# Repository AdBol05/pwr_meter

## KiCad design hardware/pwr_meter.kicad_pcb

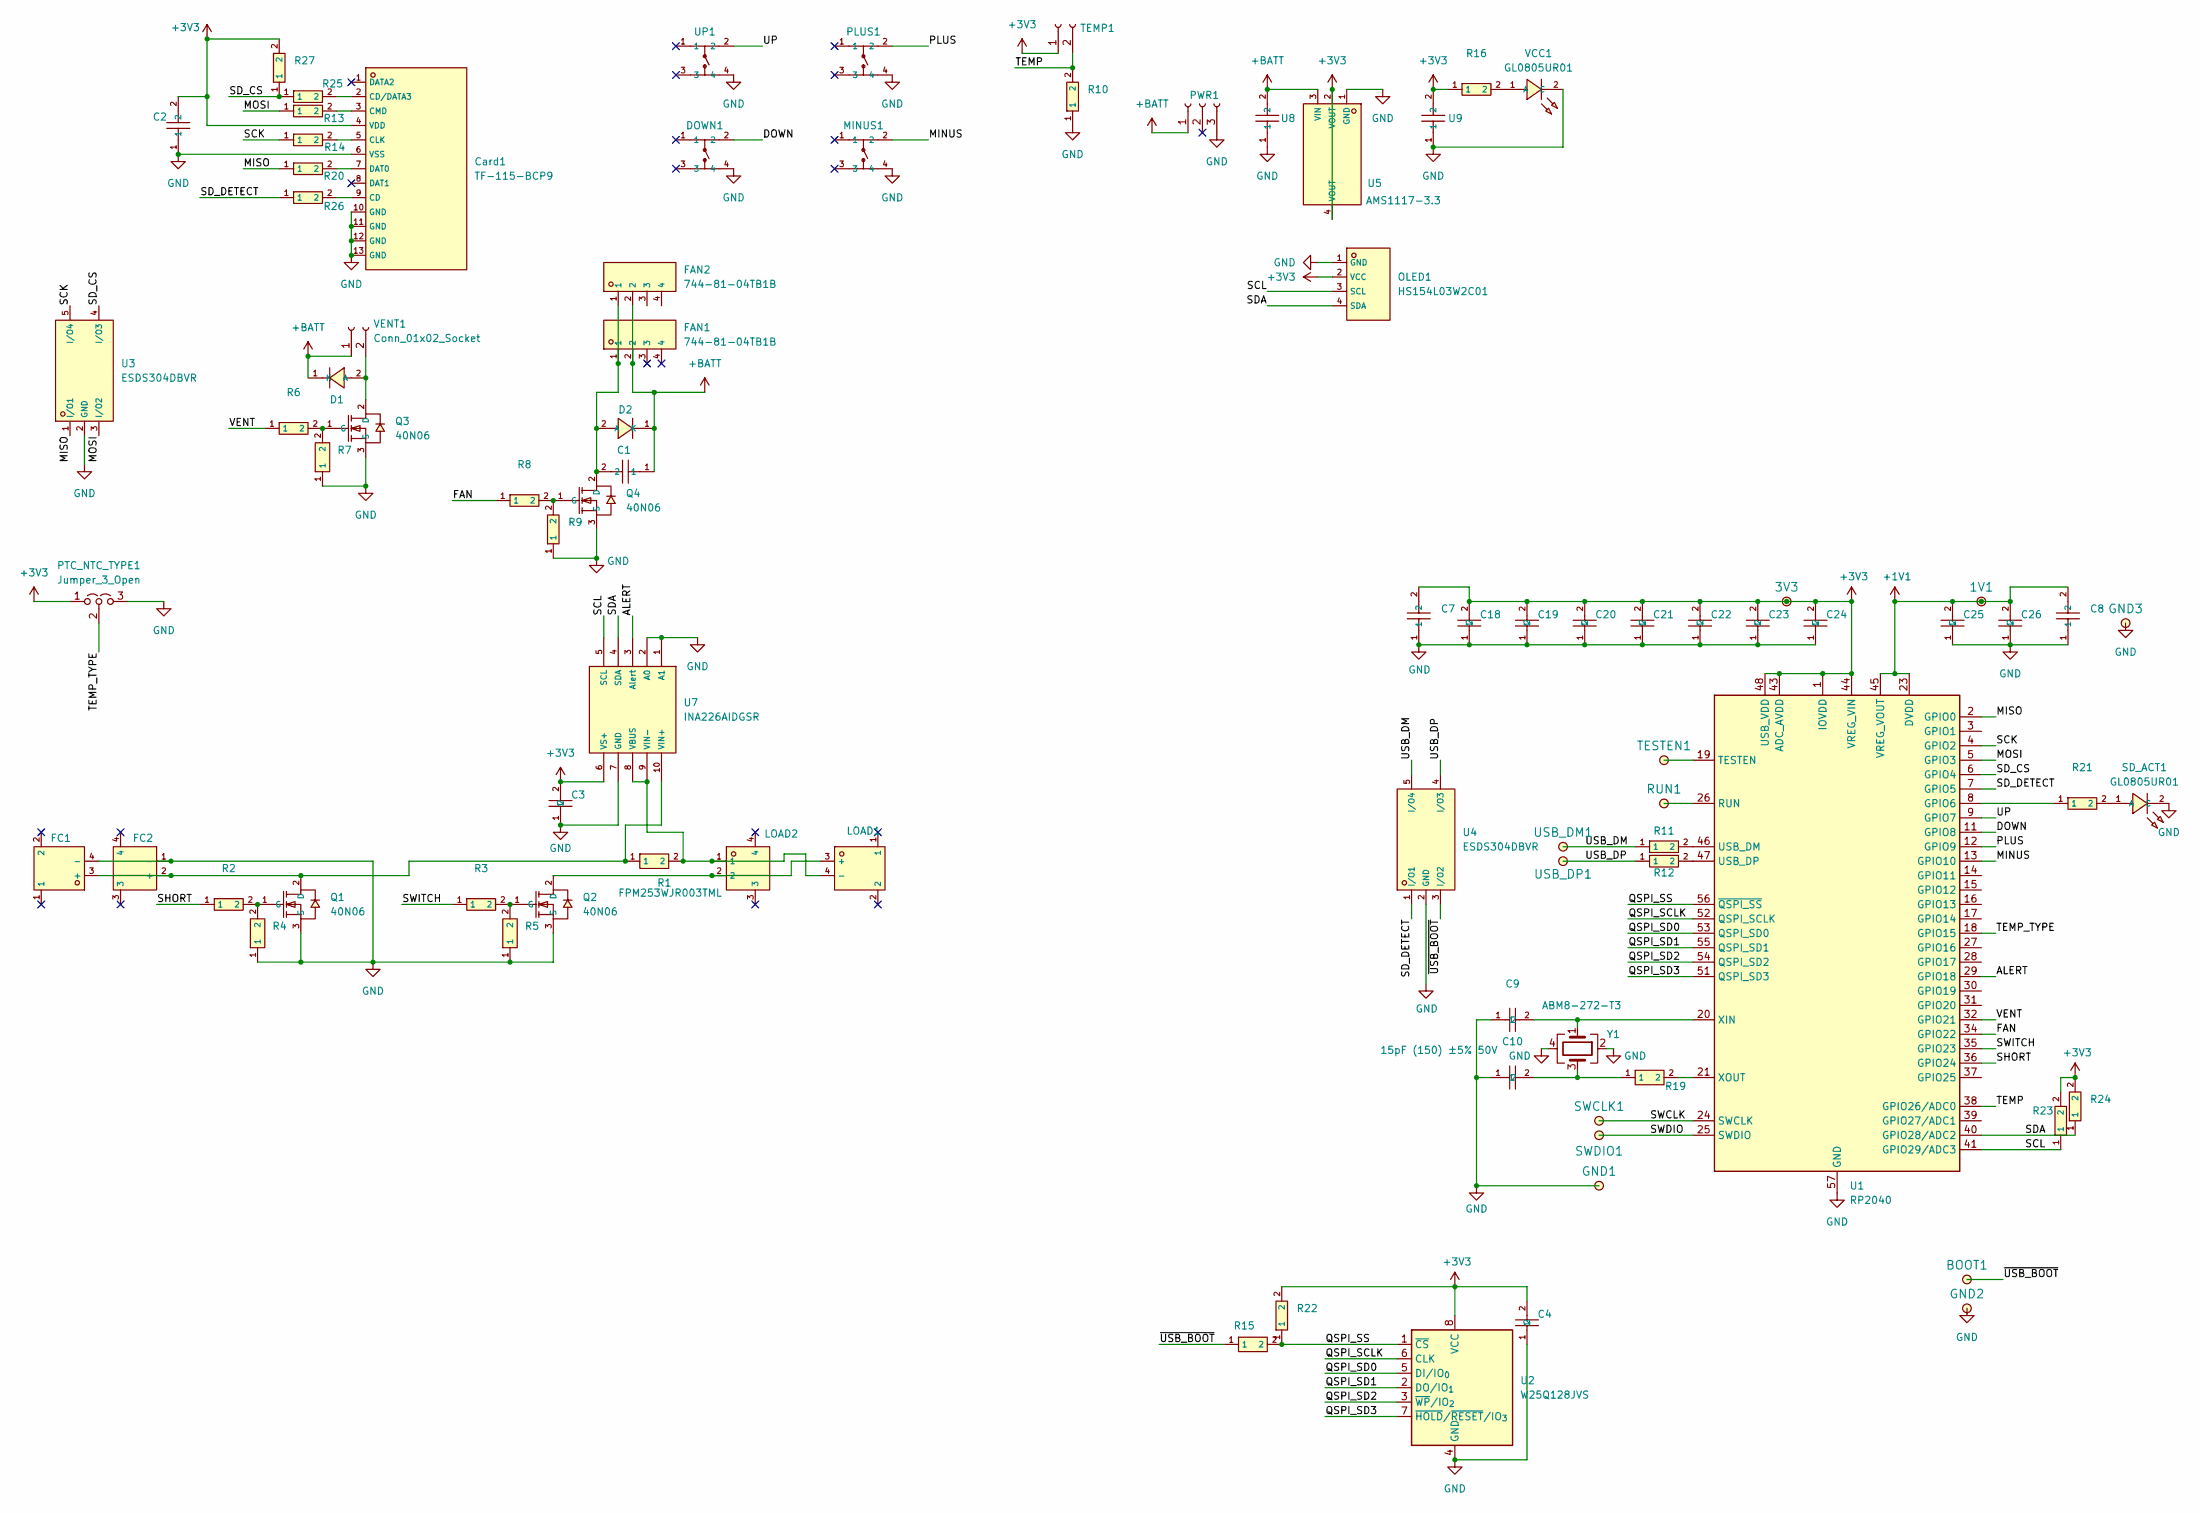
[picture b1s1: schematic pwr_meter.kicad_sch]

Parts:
1V1, 3V3: ${FAMILY}; TestPoint_Pad_1.0x1.0mm
BOOT1: ${FAMILY}; TestPoint_Pad_1.0x1.0mm
C1, C2: LMK107BBJ106MALT; C195004_C0603; LCSC C195004
C3, C4, C18, C19, C20, C21, C22, C23, C24, C25, C26: CC0603JRX7R9BB104; C91183_C0603; LCSC C91183
C7, C8: 2F01MC105B3K7D0; C54824954_C0603; LCSC C54824954
C9, C10: 15pF (150) ±5% 50V; C1644_C0603; LCSC C1644
Card1: TF-115-BCP9; C720505_TF-SMD_TF-115-BCP9; LCSC C720505
D1, D2: 1N4007_C2892681; C2892681_SOD-123FL_L2_8-W1_8-LS3_7-RD; LCSC C2892681
DOWN1: TS1103S-12X12X7.5DIP; C48677982_SW-TH_4P-L12_0-W12_0-P5_00-LS12_5; LCSC C48677982
FAN1, FAN2: 744-81-04TB1B; C402774_CONN-TH_4P-P2_54-V-M_744-81-04TXXX; LCSC C402774
FC1: FC1; C428722_TH_2P-XT60PW-F; LCSC C428722
FC2: XT30PW-M; C431092_CONN-TH_XT30PW-M; LCSC C431092
GND1, GND2, GND3: ${FAMILY}; TestPoint_Pad_1.0x1.0mm
LOAD1: XT60PW-F_C428722; C428722_TH_2P-XT60PW-F; LCSC C428722
LOAD2: XT30PW-F; C2913282_CONN-TH_XT30PW-F-1; LCSC C2913282
MINUS1: TS1103S-12X12X7.5DIP; C48677982_SW-TH_4P-L12_0-W12_0-P5_00-LS12_5; LCSC C48677982
OLED1: HS154L03W2C01; C7465999_OLED-TH_-4P-L42_4-W38_0-P2_54; LCSC C7465999
PLUS1: TS1103S-12X12X7.5DIP; C48677982_SW-TH_4P-L12_0-W12_0-P5_00-LS12_5; LCSC C48677982
PTC_NTC_TYPE1: Jumper_3_Open; SolderJumper-3_P1.3mm_Open_RoundedPad1.0x1.5mm
PWR1: Conn_01x03_Socket; PinSocket_1x03_P2.54mm_Vertical
Q1, Q2, Q3, Q4: 40N06; C668202_TO-252-2_L6_6-W6_1-P4_57-LS9_9-BR-CW; LCSC C668202
R1: FPM253WJR003TML; C7420043_RES-SMD_L6_3-W3_2_R2512; LCSC C7420043
R2, R3, R6, R8, R13, R14, R16, R20, R21, R25, R26: CR0603FA1000G; C100700_R0603; LCSC C100700
R4, R5, R7: FRC0603F1004TS; C2907003_R0603; LCSC C2907003
R9, R10, R22, R23, R24, R27: RTT03103JTP; C103210_R0603; LCSC C103210
R11, R12: MCR03ERTJ270; C308128_R0603; LCSC C308128
R15, R19: HRC0603J102 ENTN; C54920984_R0603; LCSC C54920984
RUN1: ${FAMILY}; TestPoint_Pad_1.0x1.0mm
SD_ACT1: GL0805UR01; C51933307_LED0805-R-RD_RED; LCSC C51933307
SWCLK1: ${FAMILY}; TestPoint_Pad_1.0x1.0mm
SWDIO1: ${FAMILY}; TestPoint_Pad_1.0x1.0mm
TEMP1: Conn_01x02_Socket; PinSocket_1x02_P2.54mm_Vertical
TESTEN1: ${FAMILY}; TestPoint_Pad_1.0x1.0mm
U1: RP2040; QFN-56-1EP_7x7mm_P0.4mm_EP3.2x3.2mm
U2: W25Q128JVS; SOIC-8_5.3x5.3mm_P1.27mm
U3, U4: ESDS304DBVR; C1847869_SOT-23-5_L2_9-W1_6-P0_95-LS2_8-BR; LCSC C1847869
U5: AMS1117-3.3; C6186_SOT-223-3_L6_5-W3_4-P2_30-LS7_0-BR; LCSC C6186
U7: INA226AIDGSR; C49851_MSOP-10_L3_0-W3_0-P0_50-LS5_0-BL; LCSC C49851
U8, U9: HGC1210R5107M160NSVK; C7432790_C1210; LCSC C7432790
UP1: TS1103S-12X12X7.5DIP; C48677982_SW-TH_4P-L12_0-W12_0-P5_00-LS12_5; LCSC C48677982
USB_DM1: ${FAMILY}; TestPoint_Pad_1.0x1.0mm
USB_DP1: ${FAMILY}; TestPoint_Pad_1.0x1.0mm
VCC1: GL0805UR01; C51933307_LED0805-R-RD_RED; LCSC C51933307
VENT1: Conn_01x02_Socket; PinSocket_1x02_P2.54mm_Vertical
Y1: ABM8-272-T3; Crystal_SMD_3225-4Pin_3.2x2.5mm

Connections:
+1V1: 1V1.1 (1_1), C8.2, C25.2, C26.2, U1.23 (DVDD), U1.45 (VREG_VOUT), U1.50 (DVDD)
+3V3: 3V3.1 (1_1), C2.2, C3.2, C4.2, C7.2, C18.2, C19.2, C20.2, C21.2, C22.2, C23.2, C24.2, Card1.4 (VDD), OLED1.2 (VCC), PTC_NTC_TYPE1.1 (A), R16.1, R22.2, R23.2, R24.2, R27.2, TEMP1.1, U1.1 (IOVDD), U1.10 (IOVDD), U1.22 (IOVDD), U1.33 (IOVDD), U1.42 (IOVDD), U1.43 (ADC_AVDD), U1.44 (VREG_VIN), U1.48 (USB_VDD), U1.49 (IOVDD), U2.8 (VCC), U5.2 (VOUT), U5.4 (VOUT), U7.6 (VS+), U9.2
+BATT: C1.1, D1.1 (K), D2.1 (K), FAN1.2, FAN2.2, PWR1.1, U5.3 (VIN), U8.2, VENT1.1
/ALERT: U1.29 (GPIO18), U7.3 (Alert)
/DOWN: DOWN1.2, U1.11 (GPIO8)
/FAN: R8.1, U1.34 (GPIO22)
/MINUS: MINUS1.2, U1.13 (GPIO10)
/MISO: R20.1, U1.2 (GPIO0), U3.1 (I/O1)
/MOSI: R13.1, U1.5 (GPIO3), U3.3 (I/O2)
/PLUS: PLUS1.2, U1.12 (GPIO9)
/QSPI_SCLK: U1.52 (QSPI_SCLK), U2.6 (CLK)
/QSPI_SD0: U1.53 (QSPI_SD0), U2.5 (DI/IO_{0})
/QSPI_SD1: U1.55 (QSPI_SD1), U2.2 (DO/IO_{1})
/QSPI_SD2: U1.54 (QSPI_SD2), U2.3 (~WP/IO_{2})
/QSPI_SD3: U1.51 (QSPI_SD3), U2.7 (~HOLD/~RESET/IO_{3})
/QSPI_SS: R15.2, R22.1, U1.56 (~QSPI_SS), U2.1 (~CS)
/SCK: R14.1, U1.4 (GPIO2), U3.5 (I/O4)
/SCL: OLED1.3 (SCL), R23.1, U1.41 (GPIO29/ADC3), U7.5 (SCL)
/SDA: OLED1.4 (SDA), R24.1, U1.40 (GPIO28/ADC2), U7.4 (SDA)
/SD_CS: R25.1, R27.1, U1.6 (GPIO4), U3.4 (I/O3)
/SD_DETECT: R26.1, U1.7 (GPIO5), U4.1 (I/O1)
/SHORT: R2.1, U1.36 (GPIO24)
/SWCLK: SWCLK1.1 (1_1), U1.24 (SWCLK)
/SWDIO: SWDIO1.1 (1_1), U1.25 (SWDIO)
/SWITCH: R3.1, U1.35 (GPIO23)
/TEMP: R10.2, TEMP1.2, U1.38 (GPIO26/ADC0)
/TEMP_TYPE: PTC_NTC_TYPE1.2 (C), U1.18 (GPIO15)
/UP: U1.9 (GPIO7), UP1.2
/USB_DM: R11.1, U4.5 (I/O4), USB_DM1.1 (1_1)
/USB_DP: R12.1, U4.4 (I/O3), USB_DP1.1 (1_1)
/VENT: R6.1, U1.32 (GPIO21)
/~USB_BOOT: BOOT1.1 (1_1), R15.1, U4.3 (I/O2)
GND: C2.1, C3.1, C4.1, C7.1, C8.1, C9.1, C10.1, C18.1, C19.1, C20.1, C21.1, C22.1, C23.1, C24.1, C25.1, C26.1, Card1.6 (VSS), Card1.10 (GND), Card1.11 (GND), Card1.12 (GND), Card1.13 (GND), DOWN1.4, FC1.4 (-), FC2.1 (-), GND1.1 (1_1), GND2.1 (1_1), GND3.1 (1_1), MINUS1.4, OLED1.1 (GND), PLUS1.4, PTC_NTC_TYPE1.3 (B), PWR1.3, Q1.3 (S), Q2.3 (S), Q3.3 (S), Q4.3 (S), R4.1, R5.1, R7.1, R9.1, R10.1, SD_ACT1.2 (C), U1.57 (GND), U2.4 (GND), U3.2 (GND), U4.2 (GND), U5.1 (GND), U7.1 (A1), U7.2 (A0), U7.7 (GND), U8.1, U9.1, UP1.4, VCC1.2 (C), Y1.2, Y1.4
unnamed: C10.2, R19.1, Y1.3
unnamed: Card1.9 (CD), R26.2
unnamed: Card1.2 (CD/DATA3), R25.2
unnamed: Card1.5 (CLK), R14.2
unnamed: Card1.3 (CMD), R13.2
unnamed: Card1.7 (DAT0), R20.2
unnamed: D1.2 (A), Q3.2 (D), VENT1.2
unnamed: C1.2, D2.2 (A), FAN1.1, FAN2.1, Q4.2 (D)
unnamed: FC1.3 (+), FC2.2 (+), Q1.2 (D), R1.1, U7.10 (VIN+)
unnamed: LOAD1.3 (+), LOAD2.2, Q2.2 (D)
unnamed: LOAD1.4 (-), LOAD2.1, R1.2, U7.8 (VBUS), U7.9 (VIN-)
unnamed: Q1.1 (G), R2.2, R4.2
unnamed: Q2.1 (G), R3.2, R5.2
unnamed: Q3.1 (G), R6.2, R7.2
unnamed: Q4.1 (G), R8.2, R9.2
unnamed: R21.2, SD_ACT1.1 (A)
unnamed: R21.1, U1.8 (GPIO6)
unnamed: RUN1.1 (1_1), U1.26 (RUN)
unnamed: TESTEN1.1 (1_1), U1.19 (TESTEN)
unnamed: R11.2, U1.46 (USB_DM)
unnamed: R12.2, U1.47 (USB_DP)
unnamed: C9.2, U1.20 (XIN), Y1.1
unnamed: R19.2, U1.21 (XOUT)
unnamed: R16.2, VCC1.1 (A)

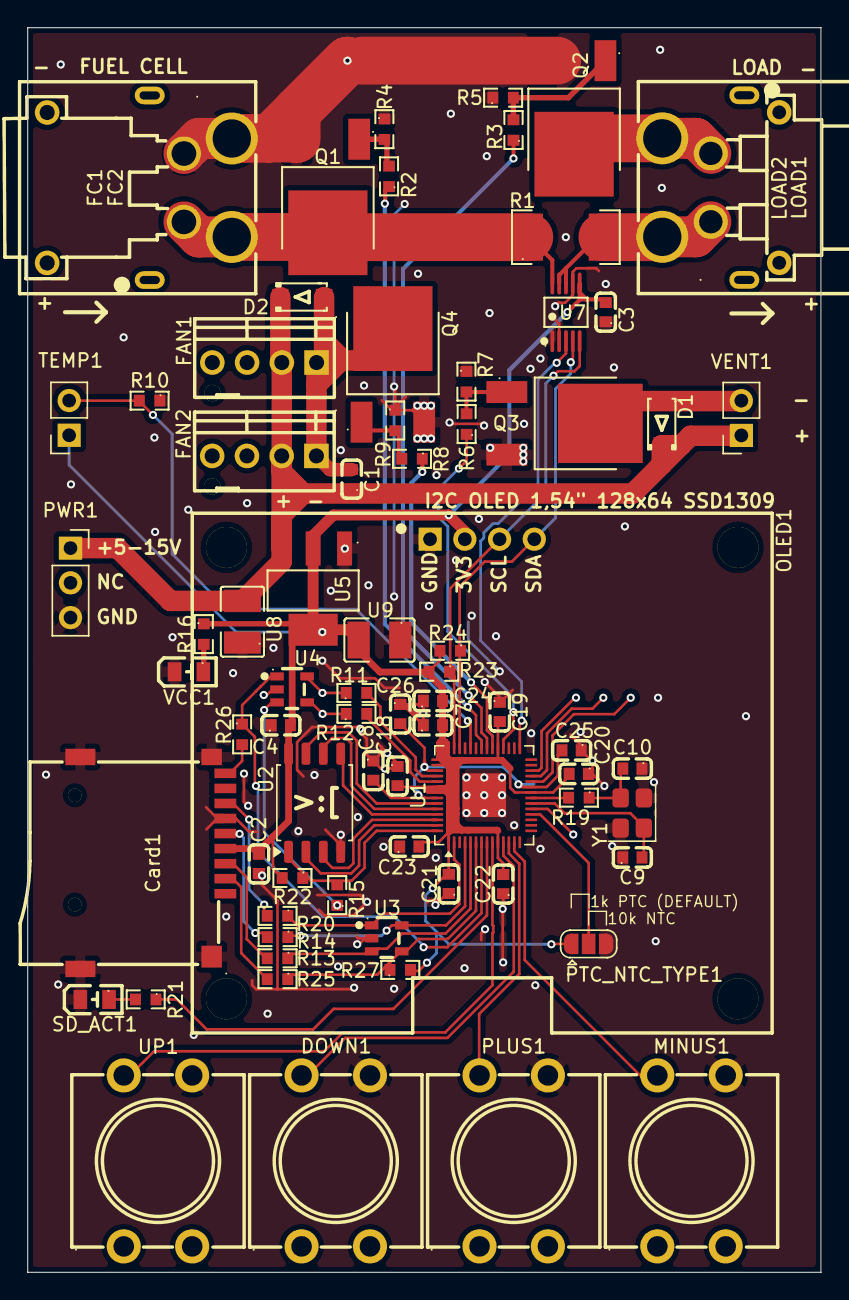
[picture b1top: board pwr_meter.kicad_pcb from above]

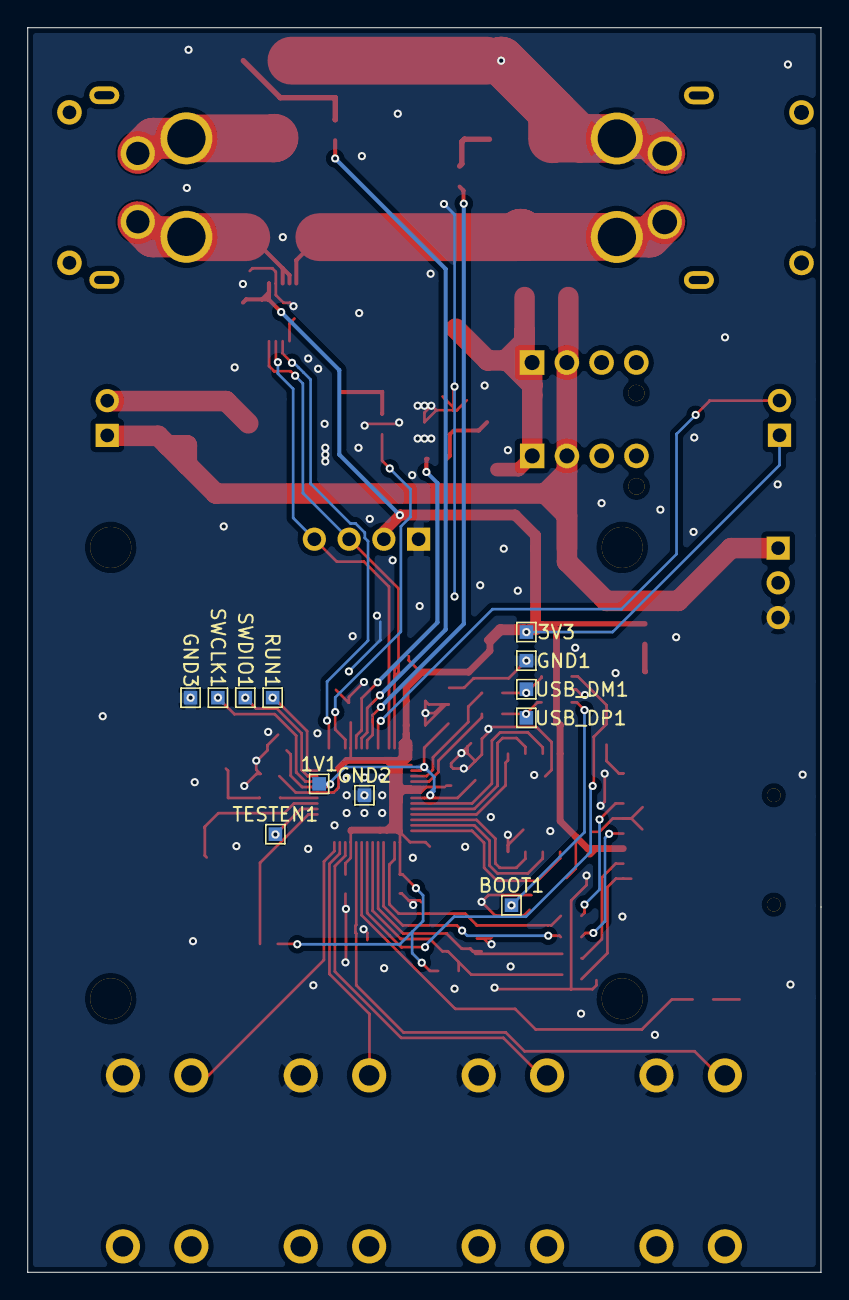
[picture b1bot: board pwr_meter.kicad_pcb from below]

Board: 2 copper layers, 58.0 x 91.0 mm, 87 parts (12 on the bottom side), 57 nets.

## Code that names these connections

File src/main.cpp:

#include "api/String.h"
#include <Arduino.h>
#include <Wire.h>
#include <INA226.h>
#include <Adafruit_GFX.h>
#include <DIYables_OLED_SSD1309.h>
//#include <U8g2lib.h>

INA226 ina(0x40);
DIYables_OLED_SSD1309 display(128, 64, &Wire, -1);


int targetTemp = 55;
long int vent_interval = 15000;
int vent_length = 110;
long int offset = 5000;
long int short_interval = 10000;
int short_length = 45;


long int lastVent = 0;
long int lastShort = 0;

int data[6] =       {55, 15000, 110, 5000, 10000, 45};
int increments[6] = {1, 1000, 10, 1000, 1000, 1};

int cursor = 0;

#define VENT 6
#define SHORT 7
#define SWITCH 8
#define TEMP 26
#define FAN 25

#define PLUS 10
#define MINUS 11
#define UP 12
#define DOWN 13

#define MISO 0
#define SCK 2
#define MOSI 3
#define SD_CS 4
#define SD_DETECT 5
#define SD_LED 9

#define TEMP_TYPE 15

bool inastatus = false;

#define R_NTC 10000.0
#define R0_NTC 10000.0
#define T0_NTC 298.15
#define BETA_NTC 3950.0

float readVoltage(int pin) {return (analogRead(pin) * 3.3) / 4095;}
float readNTC(int pin) {
  float r = R_NTC * (3.3 / readVoltage(pin) - 1.0);
  return (1.0 / ((1.0 / T0_NTC) + (1.0 / BETA_NTC) * log(r / R0_NTC))) - 273.15;
}

void setup() {
  Wire.setSDA(28); //20
  Wire.setSCL(29); //21
  Wire.begin();

  analogReadResolution(12);

  pinMode(VENT, OUTPUT);
  pinMode(SHORT, OUTPUT);
  pinMode(FAN, OUTPUT);
  pinMode(SWITCH, OUTPUT);

  /*Wire.write(0x0F);
  Wire.write(0x01);*/
  Wire.endTransmission();

  inastatus = ina.begin();
  ina.setMaxCurrentShunt(8.0, 0.01);

  Serial.begin(115200);
//  Serial.println("oled init...");
  
  if(!display.begin(SSD1309_SWITCHCAPVCC, 0x3C)){/*Serial.println("Failed to initialize oled");*/}
  display.clearDisplay();
  
  analogWrite(FAN, 255);
  digitalWrite(VENT, LOW);
  digitalWrite(SHORT, LOW);
  delay(100);
  digitalWrite(SWITCH, HIGH);

  Serial.println("Time, Voltage, Current");
}

void setup1(){
  delay(2000);

  pinMode(UP, INPUT_PULLUP);
  pinMode(DOWN, INPUT_PULLUP);
  pinMode(PLUS, INPUT_PULLUP);
  pinMode(MINUS, INPUT_PULLUP);
}


void update(){
  if(data[cursor] <= 0){data[cursor] = increments[cursor];}
  if (cursor > 5){cursor = 0;}
  if (cursor < 0){cursor = 5;}
  delay(150);
}

void loop1(){
  if(millis() - lastVent > vent_interval){
    lastVent = millis() - 1;
    digitalWrite(VENT, HIGH);
    delay(vent_length);
    digitalWrite(VENT, LOW);
  }

  if(millis() - lastShort > short_interval){
    lastShort = millis() - 1;
    digitalWrite(SWITCH, LOW);
    delay(3);
    digitalWrite(SHORT, HIGH);
    delay(short_length);
    digitalWrite(SHORT, LOW);
    delay(3);
    digitalWrite(SWITCH, HIGH);
  }

  if(digitalRead(DOWN) == LOW){cursor++; update();}
  if(digitalRead(UP) == LOW){cursor--; update();}
  if(digitalRead(PLUS) == LOW){data[cursor] = data[cursor] + increments[cursor]; update();}
  if(digitalRead(MINUS) == LOW){data[cursor] = data[cursor] - increments[cursor]; update();}
  delay(10);
}

void loop() {
  if(inastatus){
    float voltage = ina.getBusVoltage();
    float current = ina.getCurrent();
    float temp = readNTC(TEMP);
  
    /*if(voltage < 6.5){digitalWrite(19, LOW); delay(3000);}
    else {digitalWrite(19, HIGH);}*/

    display.clearDisplay();
    display.setTextSize(1);                  // 6x8 pixels per character
    display.setTextColor(SSD1309_PIXEL_ON);  // turn pixels on
    display.setCursor(15, 0);
    display.print(String(voltage, 2) + " V");
    display.setCursor(65, 0);
    display.print(String(current, 3) + " A");
    display.setCursor(15, 10);
    display.print(String(temp, 1) + " C");
    display.setCursor(65, 10);
    display.print(String(current*voltage, 3) + " W");
    display.setCursor(0, 17);
    display.print("---------------------");
    
    if(cursor <= 3){display.setCursor(0, 25 + (cursor*10));}
    else{display.setCursor(65, 25 + ((cursor - 4)*10));}
    display.print(">");

    display.setCursor(0, 25);
    display.print(" Tt: " + String(data[0]));
    display.setCursor(0, 35);
    display.print(" Vi: " + String(data[1] / 1000) + "s");
    display.setCursor(0, 45);
    display.print(" Vw: " + String(data[2]) + "ms");
    display.setCursor(0, 55);
    display.print(" Ofst: " + String(data[3] / 1000) + "s");
    
    
    display.setCursor(65, 25);
    display.print(" Si: " + String(data[4] / 1000) + "s");
    display.setCursor(65, 35);
    display.print(" Sw: " + String(data[5]) + "ms");

    /*display.setCursor(65, 55);
    display.print(String(cursor));*/
    
    display.display();

    Serial.print(millis());
    Serial.print(", ");
    Serial.print(String(voltage, 2));
    Serial.print(", ");
    Serial.println(String(current, 3));

    if(temp > data[0] + 5){
      if(temp > 80){analogWrite(FAN, 255);}
      else{analogWrite(FAN, 128);}
    }
    else{analogWrite(FAN, 40);}
  
    delay(500);
  }
  else{
    Serial.println("INA INIT FAILED");
    inastatus = ina.begin();
    delay(5000);
  }
}
